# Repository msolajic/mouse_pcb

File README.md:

# mouse_pcb
PCB for http://sensi.org/~svo/[m]ouse/
Project is also on GitHub, https://github.com/svofski/mouse1351

I cannot find the license information for the original repository, so this is licensed with the Unlicense, or "do whatever you want with it" license.

This is a quick release for CRX 2020, more detailed description and BOM to follow shortly.

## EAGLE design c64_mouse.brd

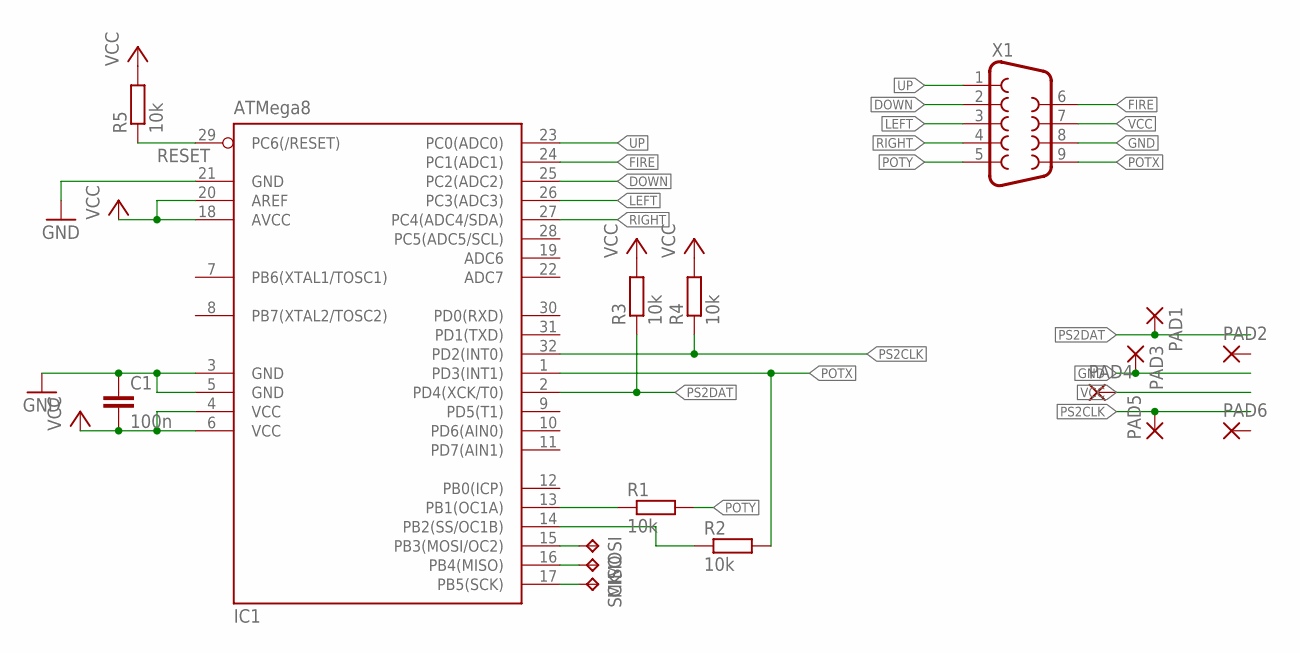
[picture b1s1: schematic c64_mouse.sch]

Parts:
C1: 100n; C0805
IC1: ATMega8; TQFP32-08
MISO: TPB1,27; B1,27
MOSI: TPB1,27; B1,27
PAD1, PAD2, PAD3, PAD4, PAD5, PAD6: SMD2; SMD1,27-2,54
R1, R2, R3, R4, R5: 10k; R0805
SCK: TPB1,27; B1,27
X1: F09D

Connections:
DOWN: IC1.25 (PC2(ADC2)), X1.2
FIRE: IC1.24 (PC1(ADC1)), X1.6
GND: C1.1, IC1.3 (GND), IC1.5 (GND), IC1.21 (GND), PAD3.1, X1.8
LEFT: IC1.26 (PC3(ADC3)), X1.3
unnamed: IC1.15 (PB3(MOSI/OC2)), MOSI.TP
unnamed: IC1.16 (PB4(MISO)), MISO.TP
unnamed: IC1.17 (PB5(SCK)), SCK.TP
unnamed: IC1.13 (PB1(OC1A)), R1.1
unnamed: IC1.14 (PB2(SS/OC1B)), R2.1
POTX: IC1.1 (PD3(INT1)), R2.2, X1.9
POTY: R1.2, X1.5
PS2CLK: IC1.32 (PD2(INT0)), PAD5.1, R4.1
PS2DAT: IC1.2 (PD4(XCK/T0)), PAD1.1, R3.1
RESET: IC1.29 (PC6(/RESET)), R5.1
RIGHT: IC1.27 (PC4(ADC4/SDA)), X1.4
UP: IC1.23 (PC0(ADC0)), X1.1
VCC: C1.2, IC1.4 (VCC), IC1.6 (VCC), IC1.18 (AVCC), IC1.20 (AREF), PAD4.1, R3.2, R4.2, R5.2, X1.7

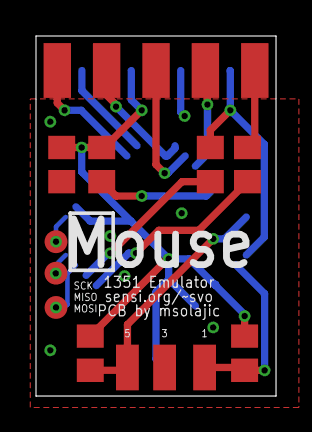
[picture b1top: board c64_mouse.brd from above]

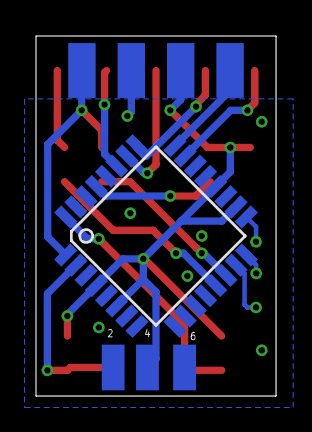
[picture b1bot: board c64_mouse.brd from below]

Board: 2 copper layers, 13.3 x 20.0 mm, 17 parts (4 on the bottom side), 17 nets.
